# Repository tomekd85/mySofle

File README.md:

It is small modification of this sofle keyboard
https://github.com/piit79/SofleKeyboard/blob/master/README.md

For the kicad files please look into:
Sofle_Choc_V3

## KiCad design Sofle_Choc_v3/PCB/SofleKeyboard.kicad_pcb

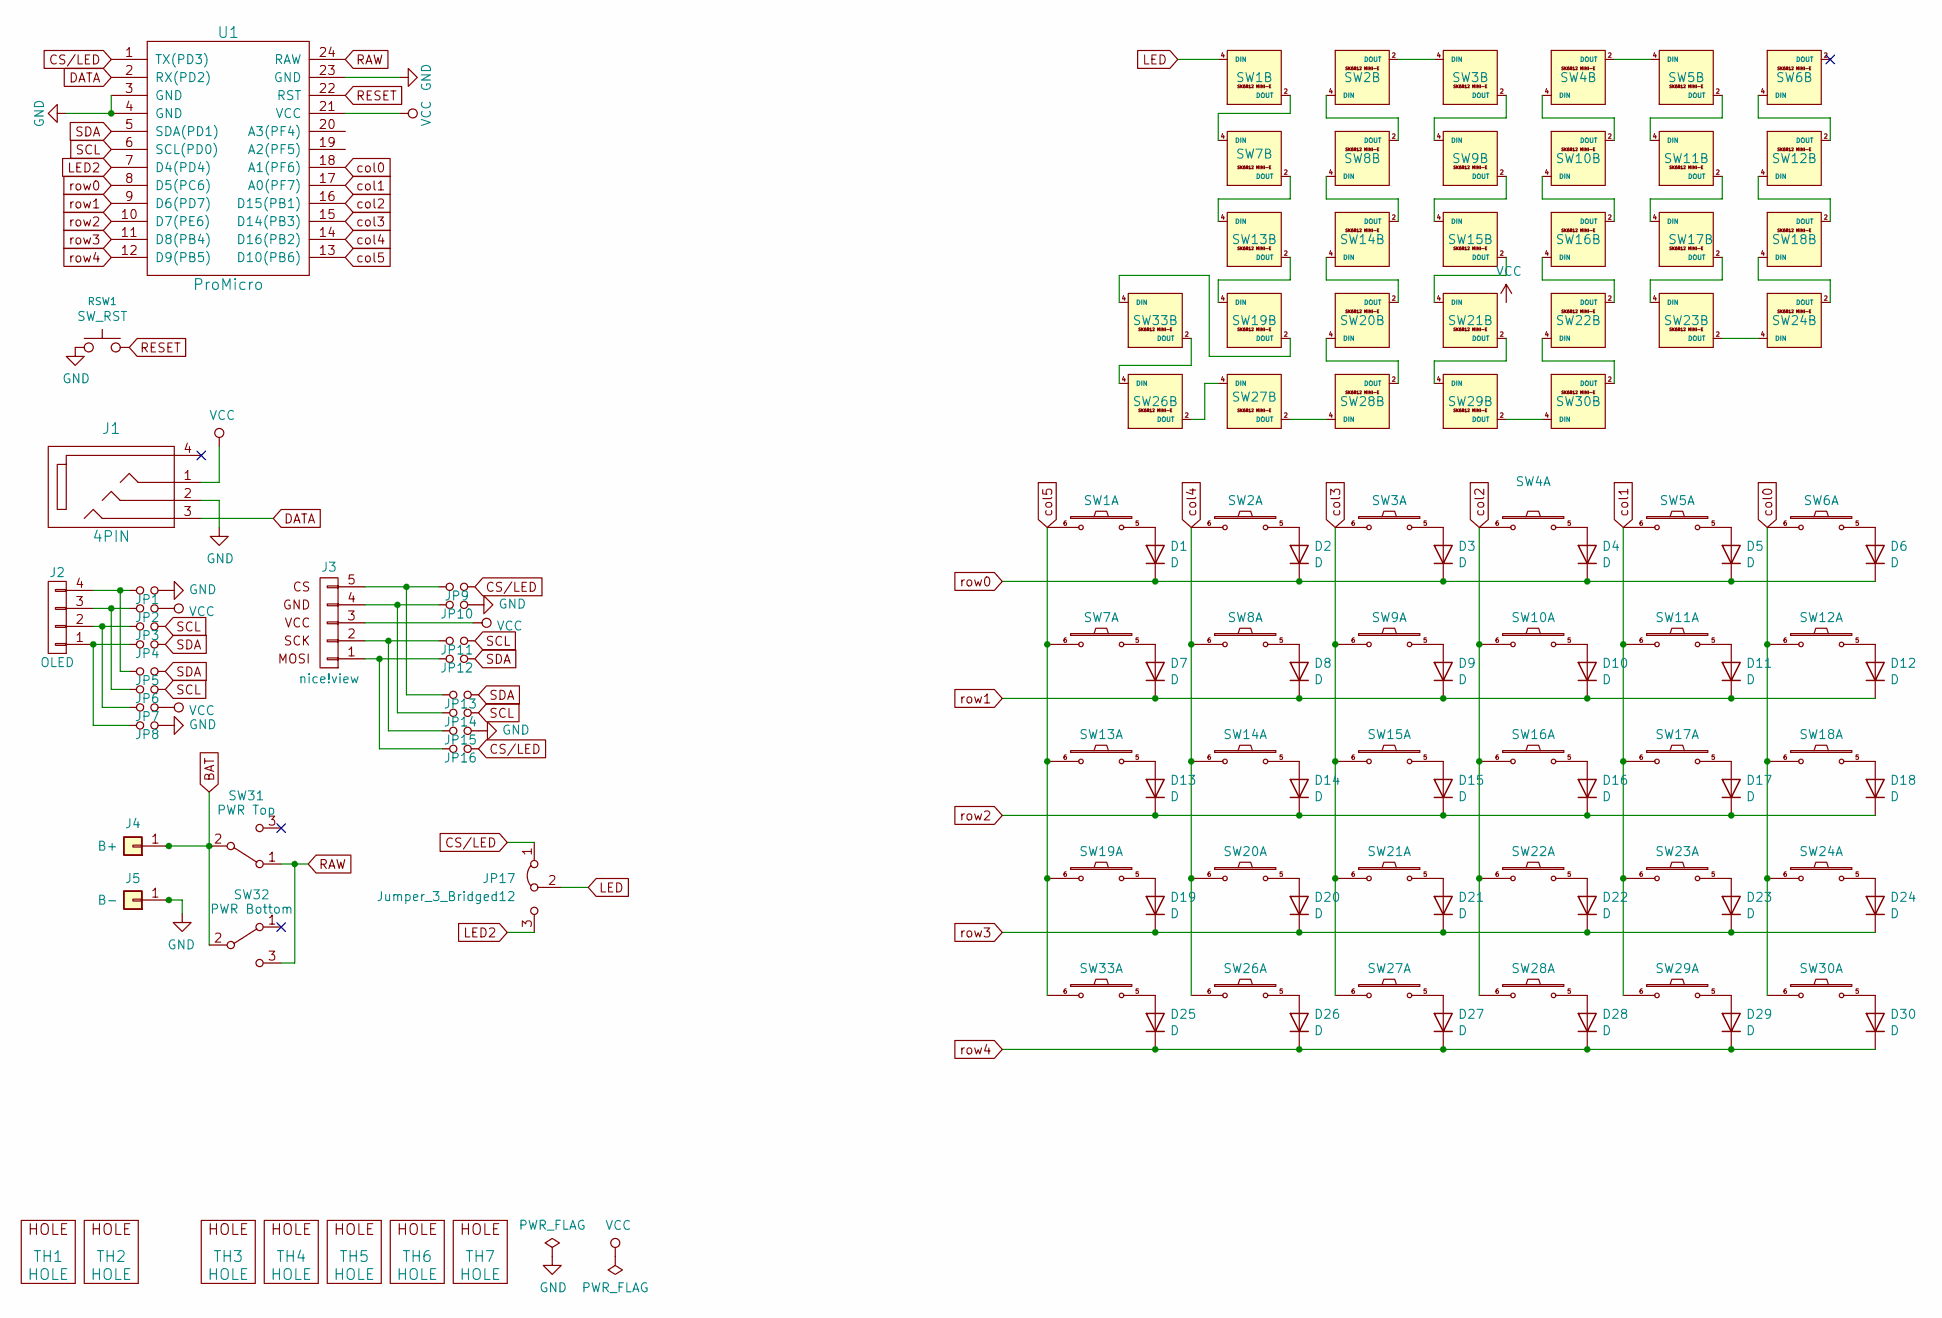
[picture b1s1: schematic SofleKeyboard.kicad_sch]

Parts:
D1, D2, D3, D4, D5, D6, D7, D8, D9, D10, D11, D12, D13, D14, D15, D16, D17, D18, D19, D20, D21, D22, D23, D24, D25, D26, D27, D28, D29, D30: D; crkbd-diode
J1: 4PIN; MJ-4PP-9
J2: OLED; OLED_4Pin
J3: nice!view; niceview_5Pin
J4: B+; PinHeader_1x01_P2.54mm_Vertical
J5: B-; PinHeader_1x01_P2.54mm_Vertical
JP1, JP2, JP3, JP4, JP5, JP6, JP7, JP8, JP9, JP10, JP11, JP12, JP13, JP14, JP15, JP16: Jumper_NO_Small; Jumper
JP17: Jumper_3_Bridged12; SolderJumper-3_P1.3mm_Bridged12_RoundedPad1.0x1.5mm_NumberL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
RSW1: SW_RST; TACT_SWITCH_TVBP06
SW1, SW2, SW3, SW4, SW5, SW6, SW7, SW8, SW9, SW10, SW11, SW12, SW13, SW14, SW15, SW16, SW17, SW18, SW19, SW20, SW21, SW22, SW23, SW24, SW26, SW27, SW28, SW29, SW30, SW33: SW_PUSH_LED; Choc_Hotswap_SK6812MiniE
SW31: PWR Top; SW_SPDT_PCM12
SW32: PWR Bottom; SW_SPDT_PCM12
TH1, TH2: HOLE; MountingHole_2.2mm_M2_ISO7380_Pad
TH3, TH4, TH5, TH6, TH7: HOLE; HOLE_M2_TH_Smaller
U1: ProMicro

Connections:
BAT: J4.1, SW31.2 (B), SW32.2 (B)
CS/LED: JP9.2, JP16.2, JP17.1 (A), U1.1 (TX(PD3))
DATA: J1.3, U1.2 (RX(PD2))
ENCA: U1.20 (A3(PF4))
ENCB: U1.19 (A2(PF5))
GND: J1.2, J5.1, JP1.2, JP8.2, JP10.2, JP15.2, RSW1.1, SW1.3 (GND), SW2.3 (GND), SW3.3 (GND), SW4.3 (GND), SW5.3 (GND), SW6.3 (GND), SW7.3 (GND), SW8.3 (GND), SW9.3 (GND), SW10.3 (GND), SW11.3 (GND), SW12.3 (GND), SW13.3 (GND), SW14.3 (GND), SW15.3 (GND), SW16.3 (GND), SW17.3 (GND), SW18.3 (GND), SW19.3 (GND), SW20.3 (GND), SW21.3 (GND), SW22.3 (GND), SW23.3 (GND), SW24.3 (GND), SW26.3 (GND), SW27.3 (GND), SW28.3 (GND), SW29.3 (GND), SW30.3 (GND), SW33.3 (GND), U1.3 (GND), U1.4 (GND), U1.23 (GND)
LED: JP17.2 (C), SW1.4 (DIN)
LED2: JP17.3 (B), U1.7 (D4(PD4))
unnamed: D1.2 (A), SW1.5
unnamed: D2.2 (A), SW2.5
unnamed: D3.2 (A), SW3.5
unnamed: D4.2 (A), SW4.5
unnamed: D5.2 (A), SW5.5
unnamed: D6.2 (A), SW6.5
unnamed: D7.2 (A), SW7.5
unnamed: D8.2 (A), SW8.5
unnamed: D9.2 (A), SW9.5
unnamed: D10.2 (A), SW10.5
unnamed: D11.2 (A), SW11.5
unnamed: D12.2 (A), SW12.5
unnamed: D13.2 (A), SW13.5
unnamed: D14.2 (A), SW14.5
unnamed: D15.2 (A), SW15.5
unnamed: D16.2 (A), SW16.5
unnamed: D17.2 (A), SW17.5
unnamed: D18.2 (A), SW18.5
unnamed: D19.2 (A), SW19.5
unnamed: D20.2 (A), SW20.5
unnamed: D21.2 (A), SW21.5
unnamed: D22.2 (A), SW22.5
unnamed: D23.2 (A), SW23.5
unnamed: D24.2 (A), SW24.5
unnamed: D25.2 (A), SW33.5
unnamed: D26.2 (A), SW26.5
unnamed: D27.2 (A), SW27.5
unnamed: D28.2 (A), SW28.5
unnamed: D29.2 (A), SW29.5
unnamed: D30.2 (A), SW30.5
unnamed: J2.1, JP4.1, JP8.1
unnamed: J2.2, JP3.1, JP7.1
unnamed: J2.3, JP2.1, JP6.1
unnamed: J2.4, JP1.1, JP5.1
unnamed: J3.1, JP12.1, JP16.1
unnamed: J3.2, JP11.1, JP15.1
unnamed: J3.4, JP10.1, JP14.1
unnamed: J3.5, JP9.1, JP13.1
unnamed: SW1.2 (DOUT), SW7.4 (DIN)
unnamed: SW2.4 (DIN), SW8.2 (DOUT)
unnamed: SW2.2 (DOUT), SW3.4 (DIN)
unnamed: SW3.2 (DOUT), SW9.4 (DIN)
unnamed: SW4.2 (DOUT), SW5.4 (DIN)
unnamed: SW10.4 (DIN), SW16.2 (DOUT)
unnamed: SW4.4 (DIN), SW10.2 (DOUT)
unnamed: SW5.2 (DOUT), SW11.4 (DIN)
unnamed: SW11.2 (DOUT), SW17.4 (DIN)
unnamed: SW12.4 (DIN), SW18.2 (DOUT)
unnamed: SW6.4 (DIN), SW12.2 (DOUT)
unnamed: SW7.2 (DOUT), SW13.4 (DIN)
unnamed: SW13.2 (DOUT), SW19.4 (DIN)
unnamed: SW14.4 (DIN), SW20.2 (DOUT)
unnamed: SW8.4 (DIN), SW14.2 (DOUT)
unnamed: SW9.2 (DOUT), SW15.4 (DIN)
unnamed: SW15.2 (DOUT), SW21.4 (DIN)
unnamed: SW16.4 (DIN), SW22.2 (DOUT)
unnamed: SW17.2 (DOUT), SW23.4 (DIN)
unnamed: SW18.4 (DIN), SW24.2 (DOUT)
unnamed: SW19.2 (DOUT), SW33.4 (DIN)
unnamed: SW20.4 (DIN), SW28.2 (DOUT)
unnamed: SW21.2 (DOUT), SW29.4 (DIN)
unnamed: SW22.4 (DIN), SW30.2 (DOUT)
unnamed: SW23.2 (DOUT), SW24.4 (DIN)
unnamed: SW26.4 (DIN), SW33.2 (DOUT)
unnamed: SW26.2 (DOUT), SW27.4 (DIN)
unnamed: SW27.2 (DOUT), SW28.4 (DIN)
unnamed: SW29.2 (DOUT), SW30.4 (DIN)
RAW: SW31.1 (A), SW32.3 (C), U1.24 (RAW)
RESET: RSW1.2, U1.22 (RST)
SCL: JP3.2, JP6.2, JP11.2, JP14.2, U1.6 (SCL(PD0))
SDA: JP4.2, JP5.2, JP12.2, JP13.2, U1.5 (SDA(PD1))
VCC: J1.1, J3.3, JP2.2, JP7.2, SW1.1 (VDD), SW2.1 (VDD), SW3.1 (VDD), SW4.1 (VDD), SW5.1 (VDD), SW6.1 (VDD), SW7.1 (VDD), SW8.1 (VDD), SW9.1 (VDD), SW10.1 (VDD), SW11.1 (VDD), SW12.1 (VDD), SW13.1 (VDD), SW14.1 (VDD), SW15.1 (VDD), SW16.1 (VDD), SW17.1 (VDD), SW18.1 (VDD), SW19.1 (VDD), SW20.1 (VDD), SW21.1 (VDD), SW22.1 (VDD), SW23.1 (VDD), SW24.1 (VDD), SW26.1 (VDD), SW27.1 (VDD), SW28.1 (VDD), SW29.1 (VDD), SW30.1 (VDD), SW33.1 (VDD), U1.21 (VCC)
col0: SW6.6, SW12.6, SW18.6, SW24.6, SW30.6, U1.18 (A1(PF6))
col1: SW5.6, SW11.6, SW17.6, SW23.6, SW29.6, U1.17 (A0(PF7))
col2: SW4.6, SW10.6, SW16.6, SW22.6, SW28.6, U1.16 (D15(PB1))
col3: SW3.6, SW9.6, SW15.6, SW21.6, SW27.6, U1.15 (D14(PB3))
col4: SW2.6, SW8.6, SW14.6, SW20.6, SW26.6, U1.14 (D16(PB2))
col5: SW1.6, SW7.6, SW13.6, SW19.6, SW33.6, U1.13 (D10(PB6))
row0: D1.1 (K), D2.1 (K), D3.1 (K), D4.1 (K), D5.1 (K), D6.1 (K), U1.8 (D5(PC6))
row1: D7.1 (K), D8.1 (K), D9.1 (K), D10.1 (K), D11.1 (K), D12.1 (K), U1.9 (D6(PD7))
row2: D13.1 (K), D14.1 (K), D15.1 (K), D16.1 (K), D17.1 (K), D18.1 (K), U1.10 (D7(PE6))
row3: D19.1 (K), D20.1 (K), D21.1 (K), D22.1 (K), D23.1 (K), D24.1 (K), U1.11 (D8(PB4))
row4: D25.1 (K), D26.1 (K), D27.1 (K), D28.1 (K), D29.1 (K), D30.1 (K), U1.12 (D9(PB5))

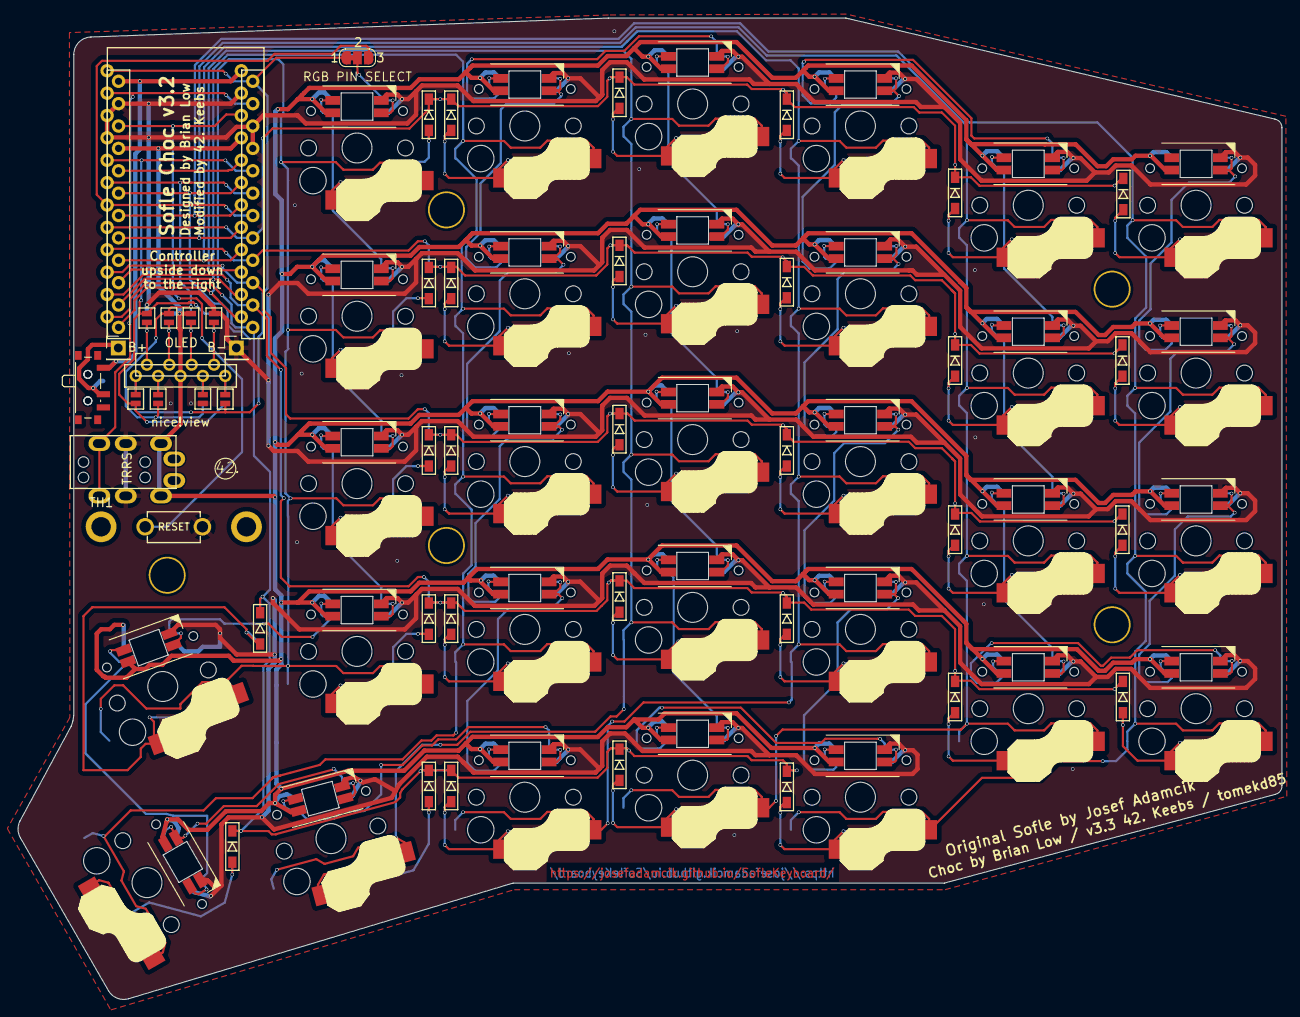
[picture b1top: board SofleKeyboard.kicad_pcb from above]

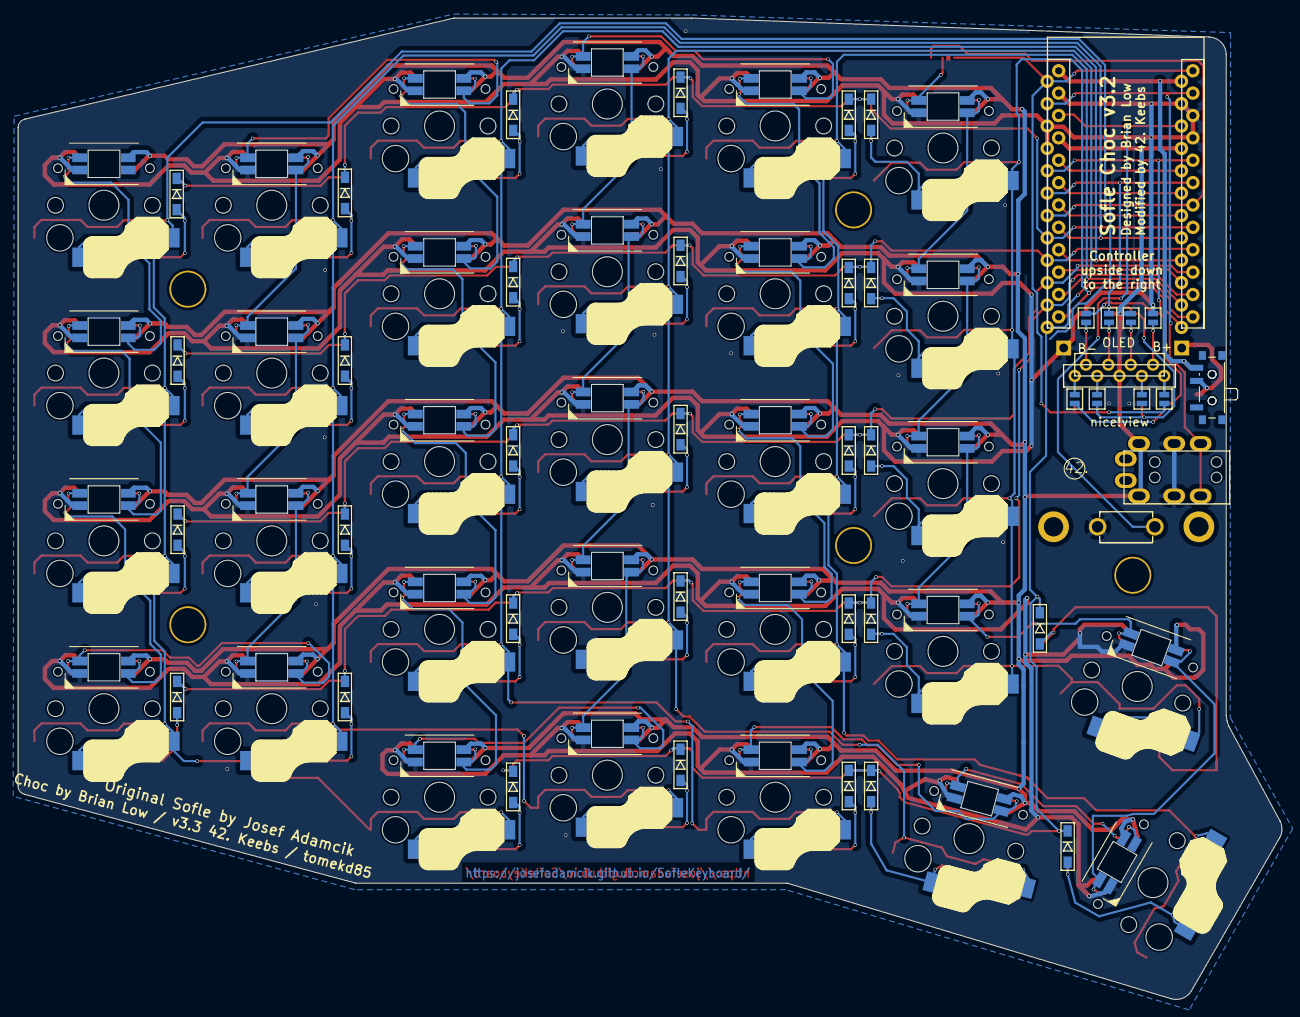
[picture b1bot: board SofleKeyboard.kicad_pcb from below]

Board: 2 copper layers, 143.5 x 111.4 mm, 93 parts (9 on the bottom side), 89 nets.

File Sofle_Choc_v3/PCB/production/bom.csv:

Designator,Footprint,Quantity,Value,LCSC Part #
"D1, D10, D11, D12, D13, D14, D15, D16, D17, D18, D19, D2, D20, D21, D22, D23, D24, D25, D26, D27, D28, D29, D3, D30, D4, D5, D6, D7, D8, D9",crkbd-diode,30,D,
J1,MJ-4PP-9,1,4PIN,
J2,OLED_4Pin,1,OLED,
J3,niceview_5Pin,1,nice!view,
J4,PinHeader_1x01_P2.54mm_Vertical,1,B+,
J5,PinHeader_1x01_P2.54mm_Vertical,1,B-,
"JP1, JP10, JP11, JP12, JP13, JP14, JP15, JP16, JP2, JP3, JP4, JP5, JP6, JP7, JP8, JP9",Jumper,16,Jumper_NO_Small,
RSW1,TACT_SWITCH_TVBP06,1,SW_RST,
"SW1, SW10, SW11, SW12, SW13, SW14, SW15, SW16, SW17, SW18, SW19, SW2, SW20, SW21, SW22, SW23, SW24, SW26, SW27, SW28, SW29, SW3, SW30, SW33, SW4, SW5, SW6, SW7, SW8, SW9",Choc_Hotswap_SK6812MiniE,30,SW_PUSH_LED,
SW31,SW_SPDT_PCM12,1,PWR Top,
SW32,SW_SPDT_PCM12,1,PWR Bottom,
"TH1, TH2",MountingHole_2.2mm_M2_ISO7380_Pad,2,HOLE,
"TH3, TH4, TH5, TH6, TH7",HOLE_M2_TH_Smaller,5,HOLE,
U1,ProMicro,1,ProMicro,

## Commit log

2024-11-13 Add sofle zip and step file
2025-04-24 Add PCB files
2025-04-24 Create LICENSE
2025-04-24 remove not needed files
2025-04-24 remove Case files
2025-04-24 add PCB
